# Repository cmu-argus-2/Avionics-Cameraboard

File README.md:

# camera-control-board
Board to control OpenMV Camera Clones.
The first draft of this board will be to create the interface between the MCU (the STM32H743IIT6) and the
similar QFP SDRAM chip, along with a USB and camera interface.

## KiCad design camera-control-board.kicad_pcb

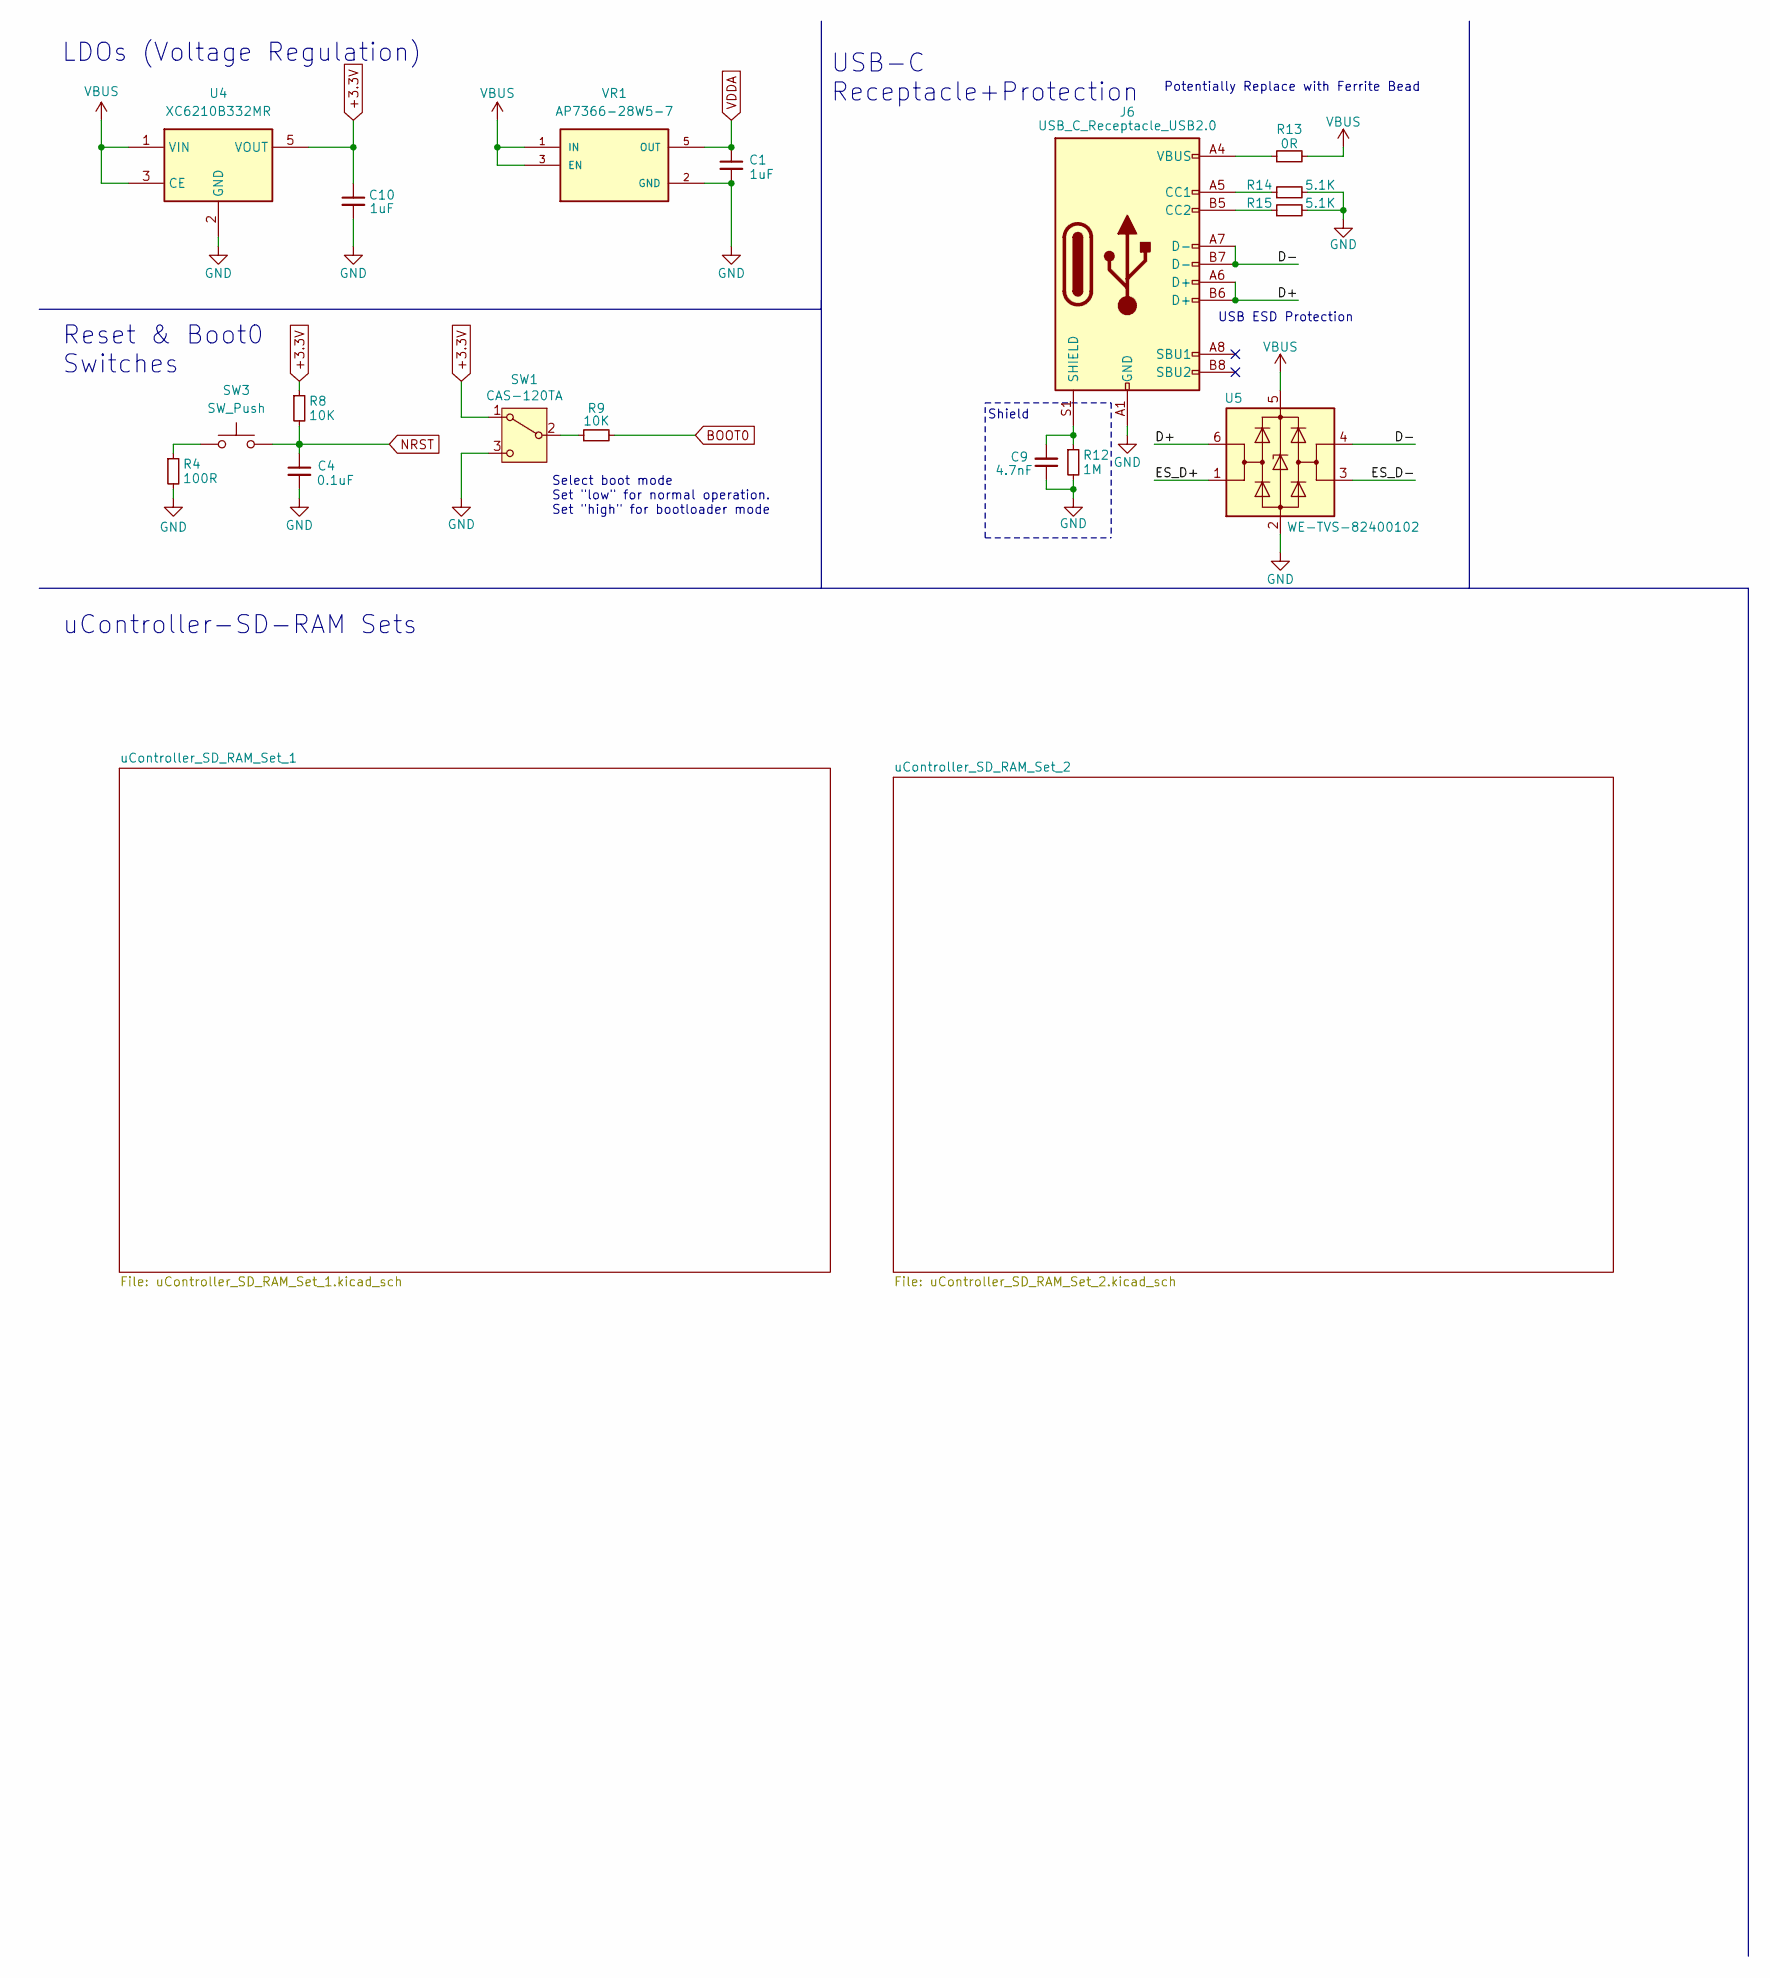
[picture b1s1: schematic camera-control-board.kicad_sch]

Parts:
C1, C10: 1uF; C_0603_1608Metric
C4: 0.1uF; C_0603_1608Metric
C9: 4.7nF; C_0603_1608Metric
J6: USB_C_Receptacle_USB2.0; USB_C_Receptacle_HRO_TYPE-C-31-M-12
R4: 100R; R_0603_1608Metric
R8, R9: 10K; R_0603_1608Metric
R12: 1M; R_0603_1608Metric
R13: 0R; R_0603_1608Metric
R14, R15: 5.1K; R_0603_1608Metric
SW1: CAS-120TA
SW3: SW_Push; BTN_KMR2
U4: XC6210B332MR; SOT-23-5
U5: WE-TVS-82400102; SOT-23-6
VR1: AP7366-28W5-7; SOT95P285X140-5N; PARTREV 1-2

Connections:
+3.3V: C10.1, R8.1, SW1.1 (A), U4.5 (VOUT); also elsewhere on the board
/D+: J6.A6 (D+), J6.B6 (D+), U5.6 (I/O1)
/D-: J6.A7 (D-), J6.B7 (D-), U5.4 (I/O2)
/ES_D+: U5.1 (I/O1)
/ES_D-: U5.3 (I/O2)
BOOT0: R9.2
GND: C1.2, C4.2, C9.1, C10.2, J6.A1 (GND), J6.A12 (GND), J6.B1 (GND), J6.B12 (GND), R4.2, R12.2, R14.2, R15.2, SW1.3 (C), U4.2 (GND), U5.2 (GND), VR1.2 (GND); also elsewhere on the board
NRST: C4.1, R8.2, SW3.2
unnamed: J6.A5 (CC1), R14.1
unnamed: J6.B5 (CC2), R15.1
unnamed: C9.2, J6.S1 (SHIELD), R12.1
unnamed: J6.A4 (VBUS), J6.A9 (VBUS), J6.B4 (VBUS), J6.B9 (VBUS), R13.1
unnamed: R4.1, SW3.1
unnamed: R9.1, SW1.2 (B)
VBUS: R13.2, U4.1 (VIN), U4.3 (CE), U5.5 (VBUS), VR1.1 (IN), VR1.3 (EN)
VDDA: C1.1, VR1.5 (OUT); also elsewhere on the board

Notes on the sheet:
LDOs (Voltage Regulation)
Shield
USB-C Receptacle+Protection
uController-SD-RAM Sets
Reset & Boot0 Switches
Potentially Replace with Ferrite Bead
USB ESD Protection
Select boot mode Set "low" for normal operation. Set "high" for bootloader mode

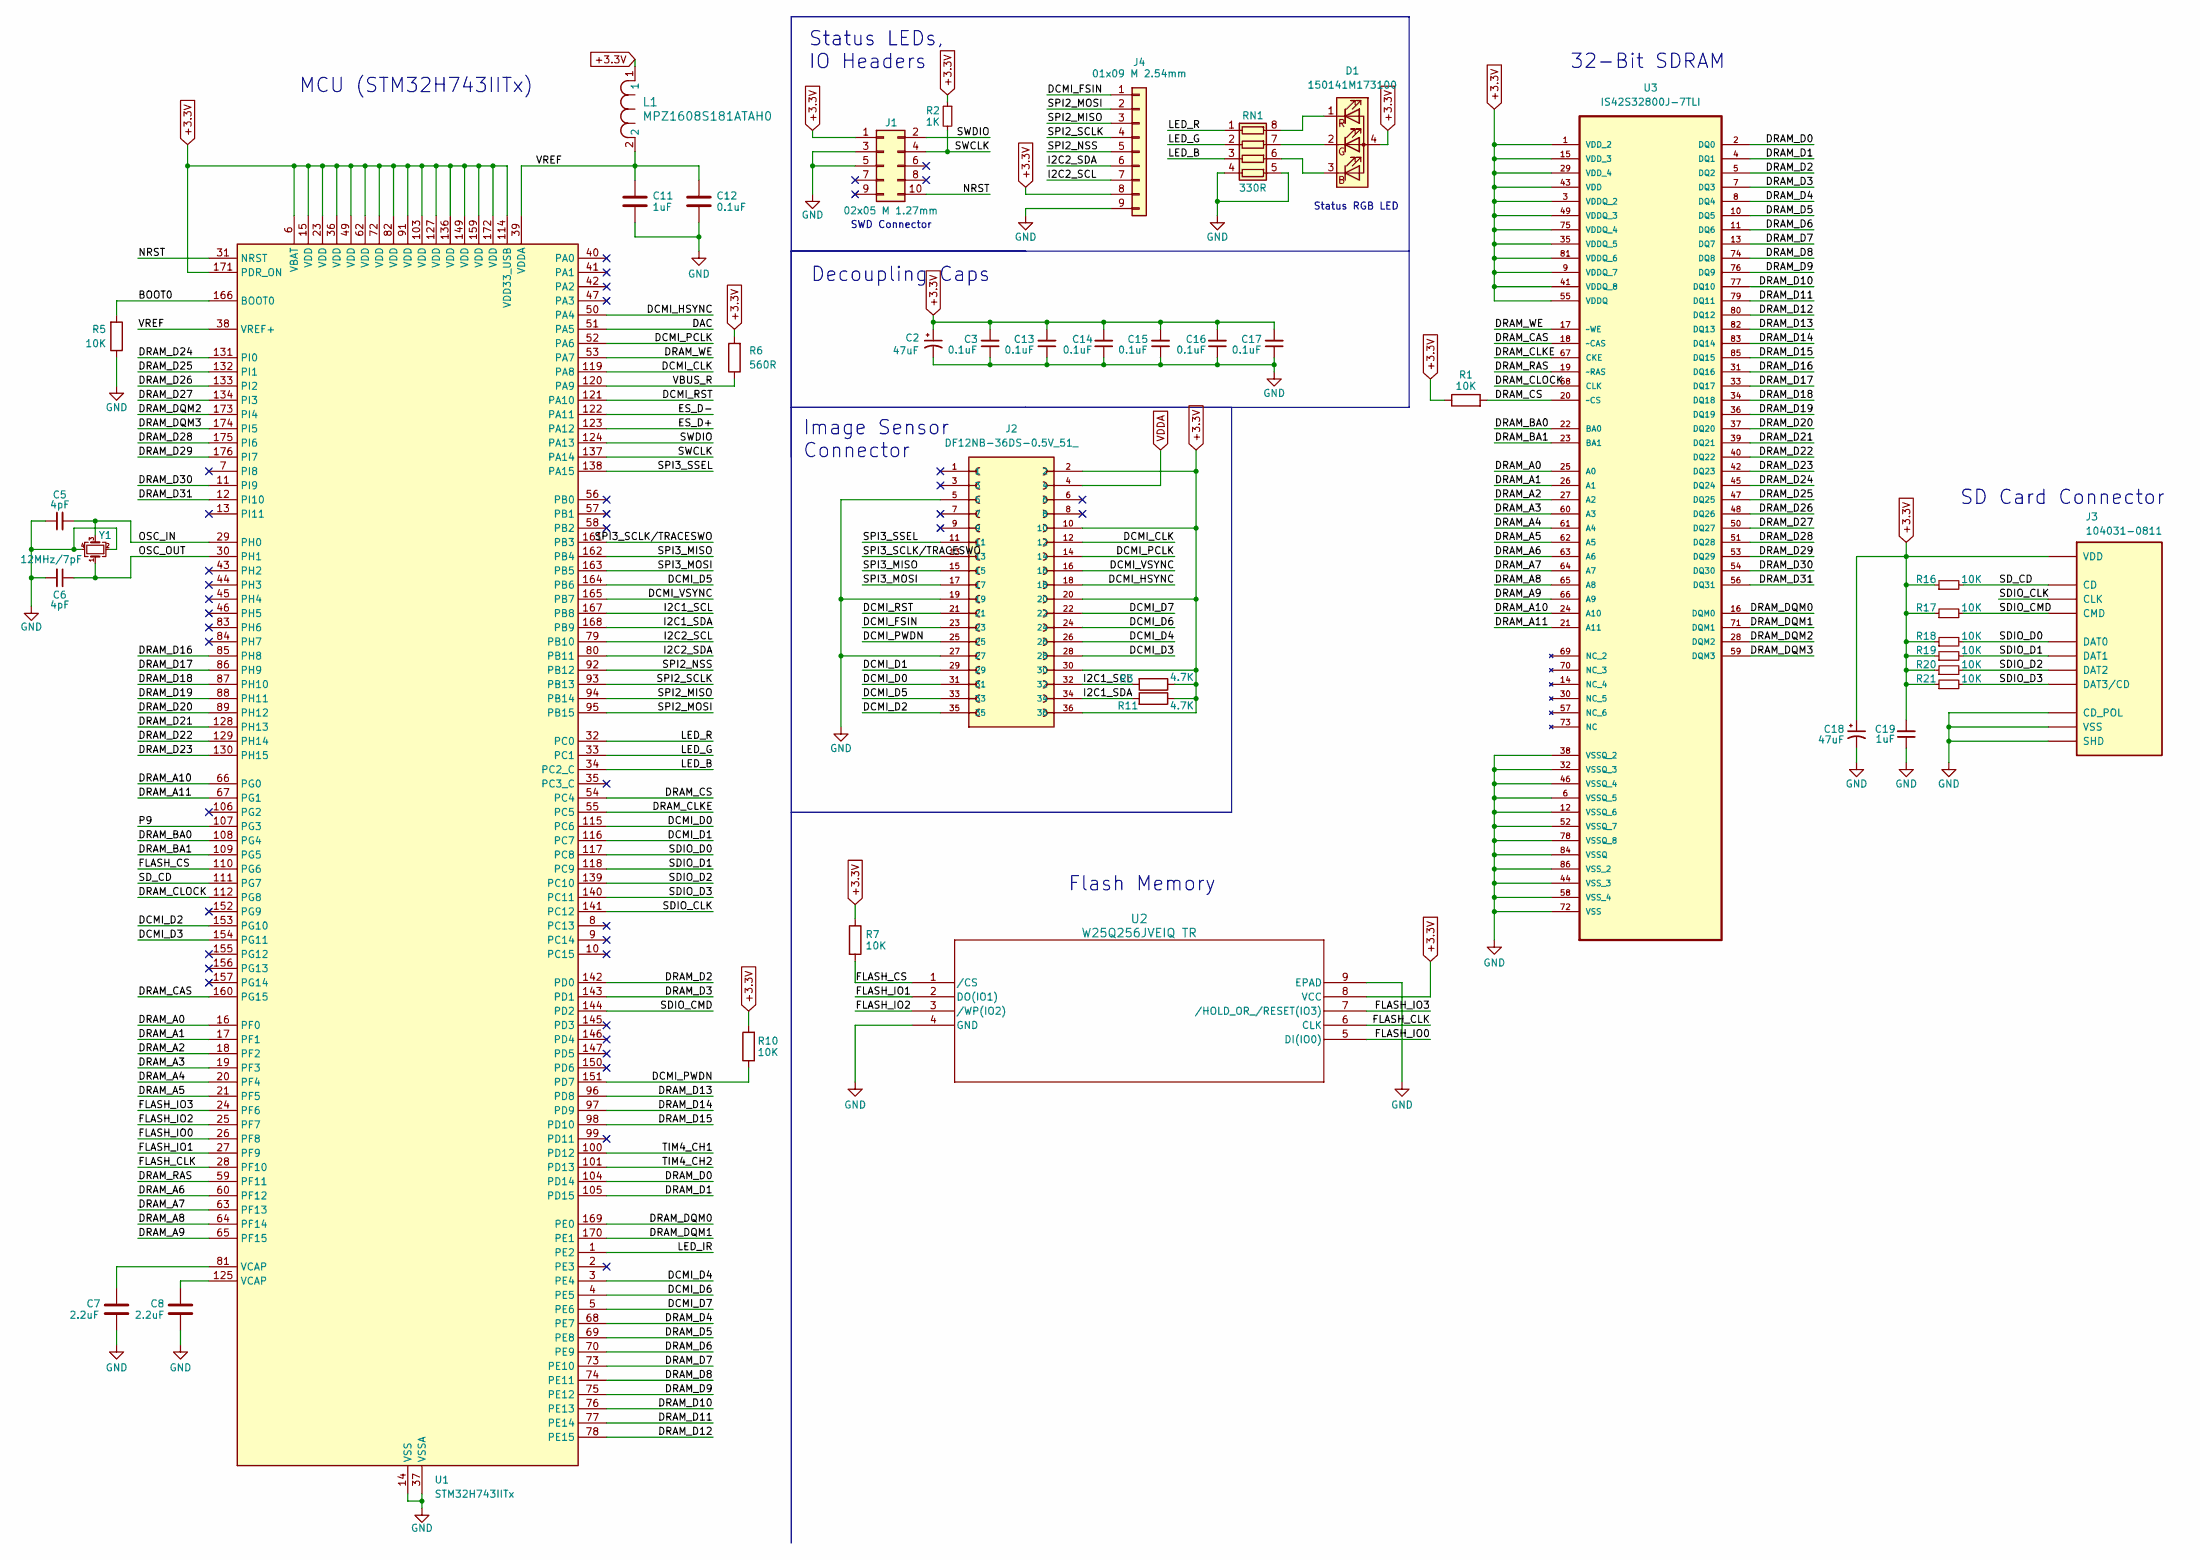
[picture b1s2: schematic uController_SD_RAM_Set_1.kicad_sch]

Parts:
C2, C18: 47uF; C_0805_2012Metric
C3, C12, C13, C14, C15, C16, C17: 0.1uF; C_0603_1608Metric
C5, C6: 4pF; C_0603_1608Metric
C7, C8: 2.2uF; C_0603_1608Metric
C11, C19: 1uF; C_0603_1608Metric
D1: 150141M173100; LED_RGB_Wuerth-PLCC4_3.2x2.8mm_150141M173100
J1: 02x05 M 1.27mm; PinHeader_2x05_P1.27mm_Vertical_SMD
J2: DF12NB-36DS-0.5V_51_; HRS_DF12NB-36DS-0.5V_51_
J3: 104031-0811; microSD_HC_Molex_104031-0811; PARTREV B2
J4: 01x09 M 2.54mm; PinHeader_1x09_P2.54mm_Vertical
L1: MPZ1608S181ATAH0; IND_1608_TDK
R1, R5, R7, R10, R16, R17, R18, R19, R20, R21: 10K; R_0603_1608Metric
R2: 1K; R_0603_1608Metric
R3, R11: 4.7K; R_0603_1608Metric
R6: 560R; R_0603_1608Metric
RN1: 330R; R_Array_Concave_4x0603
U1: STM32H743IITx; LQFP-176_24x24mm_P0.5mm
U2: W25Q256JVEIQ TR; WSON8_E_WIN-L
U3: IS42S32800J-7TLI; SOP50P1176X120-86N; MPN IS42S32800J-7TLI
Y1: 12MHz/7pF; Crystal_SMD_2520-4Pin_2.5x2.0mm

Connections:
+3.3V: C2.1, C3.2, C13.2, C14.2, C15.2, C16.2, C17.2, C18.1, C19.2, D1.4 (A), J1.1, J2.2, J2.10, J2.20, J2.30, J2.36, J3.4 (VDD), J4.8, L1.1, R1.1, R2.1, R3.1, R6.2, R7.1, R10.2, R11.1, R16.1, R17.1, R18.1, R19.1, R20.1, R21.1, U1.6 (VBAT), U1.15 (VDD), U1.23 (VDD), U1.36 (VDD), U1.49 (VDD), U1.62 (VDD), U1.72 (VDD), U1.82 (VDD), U1.91 (VDD), U1.103 (VDD), U1.114 (VDD33_USB), U1.127 (VDD), U1.136 (VDD), U1.149 (VDD), U1.159 (VDD), U1.171 (PDR_ON), U1.172 (VDD), U2.8 (VCC), U3.1 (VDD_2), U3.3 (VDDQ_2), U3.9 (VDDQ_7), U3.15 (VDD_3), U3.29 (VDD_4), U3.35 (VDDQ_5), U3.41 (VDDQ_8), U3.43 (VDD), U3.49 (VDDQ_3), U3.55 (VDDQ), U3.75 (VDDQ_4), U3.81 (VDDQ_6); also elsewhere on the board
/uController_SD_RAM_Set_1/BOOT0: R5.2, U1.166 (BOOT0)
/uController_SD_RAM_Set_1/DAC: U1.51 (PA5)
/uController_SD_RAM_Set_1/DCMI_CLK: J2.12, U1.119 (PA8)
/uController_SD_RAM_Set_1/DCMI_D0: J2.31, U1.115 (PC6)
/uController_SD_RAM_Set_1/DCMI_D1: J2.29, U1.116 (PC7)
/uController_SD_RAM_Set_1/DCMI_D2: J2.35, U1.153 (PG10)
/uController_SD_RAM_Set_1/DCMI_D3: J2.28, U1.154 (PG11)
/uController_SD_RAM_Set_1/DCMI_D4: J2.26, U1.3 (PE4)
/uController_SD_RAM_Set_1/DCMI_D5: J2.33, U1.164 (PB6)
/uController_SD_RAM_Set_1/DCMI_D6: J2.24, U1.4 (PE5)
/uController_SD_RAM_Set_1/DCMI_D7: J2.22, U1.5 (PE6)
/uController_SD_RAM_Set_1/DCMI_FSIN: J2.23, J4.1
/uController_SD_RAM_Set_1/DCMI_HSYNC: J2.18, U1.50 (PA4)
/uController_SD_RAM_Set_1/DCMI_PCLK: J2.14, U1.52 (PA6)
/uController_SD_RAM_Set_1/DCMI_PWDN: J2.25, R10.1, U1.151 (PD7)
/uController_SD_RAM_Set_1/DCMI_RST: J2.21, U1.121 (PA10)
/uController_SD_RAM_Set_1/DCMI_VSYNC: J2.16, U1.165 (PB7)
/uController_SD_RAM_Set_1/DRAM_A0: U1.16 (PF0), U3.25 (A0)
/uController_SD_RAM_Set_1/DRAM_A1: U1.17 (PF1), U3.26 (A1)
/uController_SD_RAM_Set_1/DRAM_A2: U1.18 (PF2), U3.27 (A2)
/uController_SD_RAM_Set_1/DRAM_A3: U1.19 (PF3), U3.60 (A3)
/uController_SD_RAM_Set_1/DRAM_A4: U1.20 (PF4), U3.61 (A4)
/uController_SD_RAM_Set_1/DRAM_A5: U1.21 (PF5), U3.62 (A5)
/uController_SD_RAM_Set_1/DRAM_A6: U1.60 (PF12), U3.63 (A6)
/uController_SD_RAM_Set_1/DRAM_A7: U1.63 (PF13), U3.64 (A7)
/uController_SD_RAM_Set_1/DRAM_A8: U1.64 (PF14), U3.65 (A8)
/uController_SD_RAM_Set_1/DRAM_A9: U1.65 (PF15), U3.66 (A9)
/uController_SD_RAM_Set_1/DRAM_A10: U1.66 (PG0), U3.24 (A10)
/uController_SD_RAM_Set_1/DRAM_A11: U1.67 (PG1), U3.21 (A11)
/uController_SD_RAM_Set_1/DRAM_BA0: U1.108 (PG4), U3.22 (BA0)
/uController_SD_RAM_Set_1/DRAM_BA1: U1.109 (PG5), U3.23 (BA1)
/uController_SD_RAM_Set_1/DRAM_CAS: U1.160 (PG15), U3.18 (~CAS)
/uController_SD_RAM_Set_1/DRAM_CLKE: U1.55 (PC5), U3.67 (CKE)
/uController_SD_RAM_Set_1/DRAM_CLOCK: U1.112 (PG8), U3.68 (CLK)
/uController_SD_RAM_Set_1/DRAM_CS: R1.2, U1.54 (PC4), U3.20 (~CS)
/uController_SD_RAM_Set_1/DRAM_D0: U1.104 (PD14), U3.2 (DQ0)
/uController_SD_RAM_Set_1/DRAM_D1: U1.105 (PD15), U3.4 (DQ1)
/uController_SD_RAM_Set_1/DRAM_D2: U1.142 (PD0), U3.5 (DQ2)
/uController_SD_RAM_Set_1/DRAM_D3: U1.143 (PD1), U3.7 (DQ3)
/uController_SD_RAM_Set_1/DRAM_D4: U1.68 (PE7), U3.8 (DQ4)
/uController_SD_RAM_Set_1/DRAM_D5: U1.69 (PE8), U3.10 (DQ5)
/uController_SD_RAM_Set_1/DRAM_D6: U1.70 (PE9), U3.11 (DQ6)
/uController_SD_RAM_Set_1/DRAM_D7: U1.73 (PE10), U3.13 (DQ7)
/uController_SD_RAM_Set_1/DRAM_D8: U1.74 (PE11), U3.74 (DQ8)
/uController_SD_RAM_Set_1/DRAM_D9: U1.75 (PE12), U3.76 (DQ9)
/uController_SD_RAM_Set_1/DRAM_D10: U1.76 (PE13), U3.77 (DQ10)
/uController_SD_RAM_Set_1/DRAM_D11: U1.77 (PE14), U3.79 (DQ11)
/uController_SD_RAM_Set_1/DRAM_D12: U1.78 (PE15), U3.80 (DQ12)
/uController_SD_RAM_Set_1/DRAM_D13: U1.96 (PD8), U3.82 (DQ13)
/uController_SD_RAM_Set_1/DRAM_D14: U1.97 (PD9), U3.83 (DQ14)
/uController_SD_RAM_Set_1/DRAM_D15: U1.98 (PD10), U3.85 (DQ15)
/uController_SD_RAM_Set_1/DRAM_D16: U1.85 (PH8), U3.31 (DQ16)
/uController_SD_RAM_Set_1/DRAM_D17: U1.86 (PH9), U3.33 (DQ17)
/uController_SD_RAM_Set_1/DRAM_D18: U1.87 (PH10), U3.34 (DQ18)
/uController_SD_RAM_Set_1/DRAM_D19: U1.88 (PH11), U3.36 (DQ19)
/uController_SD_RAM_Set_1/DRAM_D20: U1.89 (PH12), U3.37 (DQ20)
/uController_SD_RAM_Set_1/DRAM_D21: U1.128 (PH13), U3.39 (DQ21)
/uController_SD_RAM_Set_1/DRAM_D22: U1.129 (PH14), U3.40 (DQ22)
/uController_SD_RAM_Set_1/DRAM_D23: U1.130 (PH15), U3.42 (DQ23)
/uController_SD_RAM_Set_1/DRAM_D24: U1.131 (PI0), U3.45 (DQ24)
/uController_SD_RAM_Set_1/DRAM_D25: U1.132 (PI1), U3.47 (DQ25)
/uController_SD_RAM_Set_1/DRAM_D26: U1.133 (PI2), U3.48 (DQ26)
/uController_SD_RAM_Set_1/DRAM_D27: U1.134 (PI3), U3.50 (DQ27)
/uController_SD_RAM_Set_1/DRAM_D28: U1.175 (PI6), U3.51 (DQ28)
/uController_SD_RAM_Set_1/DRAM_D29: U1.176 (PI7), U3.53 (DQ29)
/uController_SD_RAM_Set_1/DRAM_D30: U1.11 (PI9), U3.54 (DQ30)
/uController_SD_RAM_Set_1/DRAM_D31: U1.12 (PI10), U3.56 (DQ31)
/uController_SD_RAM_Set_1/DRAM_DQM0: U1.169 (PE0), U3.16 (DQM0)
/uController_SD_RAM_Set_1/DRAM_DQM1: U1.170 (PE1), U3.71 (DQM1)
/uController_SD_RAM_Set_1/DRAM_DQM2: U1.173 (PI4), U3.28 (DQM2)
/uController_SD_RAM_Set_1/DRAM_DQM3: U1.174 (PI5), U3.59 (DQM3)
/uController_SD_RAM_Set_1/DRAM_RAS: U1.59 (PF11), U3.19 (~RAS)
/uController_SD_RAM_Set_1/DRAM_WE: U1.53 (PA7), U3.17 (~WE)
/uController_SD_RAM_Set_1/ES_D+: U1.123 (PA12)
/uController_SD_RAM_Set_1/ES_D-: U1.122 (PA11)
/uController_SD_RAM_Set_1/FLASH_CLK: U1.28 (PF10), U2.6 (CLK)
/uController_SD_RAM_Set_1/FLASH_CS: R7.2, U1.110 (PG6), U2.1 (/CS)
/uController_SD_RAM_Set_1/FLASH_IO0: U1.26 (PF8), U2.5 (DI(IO0))
/uController_SD_RAM_Set_1/FLASH_IO1: U1.27 (PF9), U2.2 (DO(IO1))
/uController_SD_RAM_Set_1/FLASH_IO2: U1.25 (PF7), U2.3 (/WP(IO2))
/uController_SD_RAM_Set_1/FLASH_IO3: U1.24 (PF6), U2.7 (/HOLD_OR_/RESET(IO3))
/uController_SD_RAM_Set_1/I2C1_SCL: J2.32, R3.2, U1.167 (PB8)
/uController_SD_RAM_Set_1/I2C1_SDA: J2.34, R11.2, U1.168 (PB9)
/uController_SD_RAM_Set_1/I2C2_SCL: J4.7, U1.79 (PB10)
/uController_SD_RAM_Set_1/I2C2_SDA: J4.6, U1.80 (PB11)
/uController_SD_RAM_Set_1/LED_B: RN1.3 (R3.1), U1.34 (PC2_C)
/uController_SD_RAM_Set_1/LED_G: RN1.2 (R2.1), U1.33 (PC1)
/uController_SD_RAM_Set_1/LED_IR: U1.1 (PE2)
/uController_SD_RAM_Set_1/LED_R: RN1.1 (R1.1), U1.32 (PC0)
/uController_SD_RAM_Set_1/NRST: J1.10, U1.31 (NRST)
/uController_SD_RAM_Set_1/OSC_IN: C5.2, U1.29 (PH0), Y1.3
/uController_SD_RAM_Set_1/OSC_OUT: C6.1, U1.30 (PH1), Y1.1
/uController_SD_RAM_Set_1/P9: U1.107 (PG3)
/uController_SD_RAM_Set_1/SDIO_CLK: J3.5 (CLK), U1.141 (PC12)
/uController_SD_RAM_Set_1/SDIO_CMD: J3.3 (CMD), R17.2, U1.144 (PD2)
/uController_SD_RAM_Set_1/SDIO_D0: J3.7 (DAT0), R18.2, U1.117 (PC8)
/uController_SD_RAM_Set_1/SDIO_D1: J3.8 (DAT1), R19.2, U1.118 (PC9)
/uController_SD_RAM_Set_1/SDIO_D2: J3.1 (DAT2), R20.2, U1.139 (PC10)
/uController_SD_RAM_Set_1/SDIO_D3: J3.2 (DAT3/CD), R21.2, U1.140 (PC11)
/uController_SD_RAM_Set_1/SD_CD: J3.10 (CD), R16.2, U1.111 (PG7)
/uController_SD_RAM_Set_1/SPI2_MISO: J4.3, U1.94 (PB14)
/uController_SD_RAM_Set_1/SPI2_MOSI: J4.2, U1.95 (PB15)
/uController_SD_RAM_Set_1/SPI2_NSS: J4.5, U1.92 (PB12)
/uController_SD_RAM_Set_1/SPI2_SCLK: J4.4, U1.93 (PB13)
/uController_SD_RAM_Set_1/SPI3_MISO: J2.15, U1.162 (PB4)
/uController_SD_RAM_Set_1/SPI3_MOSI: J2.17, U1.163 (PB5)
/uController_SD_RAM_Set_1/SPI3_SCLK/TRACESWO: J2.13, U1.161 (PB3)
/uController_SD_RAM_Set_1/SPI3_SSEL: J2.11, U1.138 (PA15)
/uController_SD_RAM_Set_1/SWCLK: J1.4, R2.2, U1.137 (PA14)
/uController_SD_RAM_Set_1/SWDIO: J1.2, U1.124 (PA13)
/uController_SD_RAM_Set_1/TIM4_CH1: U1.100 (PD12)
/uController_SD_RAM_Set_1/TIM4_CH2: U1.101 (PD13)
/uController_SD_RAM_Set_1/VBUS_R: R6.1, U1.120 (PA9)
/uController_SD_RAM_Set_1/VREF: C11.1, C12.1, L1.2, U1.38 (VREF+), U1.39 (VDDA)
GND: C2.2, C3.1, C5.1, C6.2, C7.2, C8.2, C11.2, C12.2, C13.1, C14.1, C15.1, C16.1, C17.1, C18.2, C19.1, J1.3, J1.5, J2.5, J2.19, J2.27, J3.6 (VSS), J3.9 (CD_POL), J3.11 (SHD), J4.9, R5.1, RN1.4 (R4.1), RN1.5 (R4.2), U1.14 (VSS), U1.22 (VSS), U1.37 (VSSA), U1.48 (VSS), U1.61 (VSS), U1.71 (VSS), U1.90 (VSS), U1.102 (VSS), U1.113 (VSS), U1.126 (VSS), U1.135 (VSS), U1.148 (VSS), U1.158 (VSS), U2.4 (GND), U2.9 (EPAD), U3.6 (VSSQ_5), U3.12 (VSSQ_6), U3.32 (VSSQ_3), U3.38 (VSSQ_2), U3.44 (VSS_3), U3.46 (VSSQ_4), U3.52 (VSSQ_7), U3.58 (VSS_4), U3.72 (VSS), U3.78 (VSSQ_8), U3.84 (VSSQ), U3.86 (VSS_2), Y1.2, Y1.4; also elsewhere on the board
unnamed: C7.1, U1.81 (VCAP)
unnamed: C8.1, U1.125 (VCAP)
unnamed: D1.3 (BK), RN1.6 (R3.2)
unnamed: D1.2 (GK), RN1.7 (R2.2)
unnamed: D1.1 (RK), RN1.8 (R1.2)
VDDA: J2.4; also elsewhere on the board

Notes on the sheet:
Decoupling Caps
Image Sensor Connector
Flash Memory
Status LEDs, IO Headers
SD Card Connector
SWD Connector
32-Bit SDRAM
Status RGB LED
MCU (STM32H743IITx)

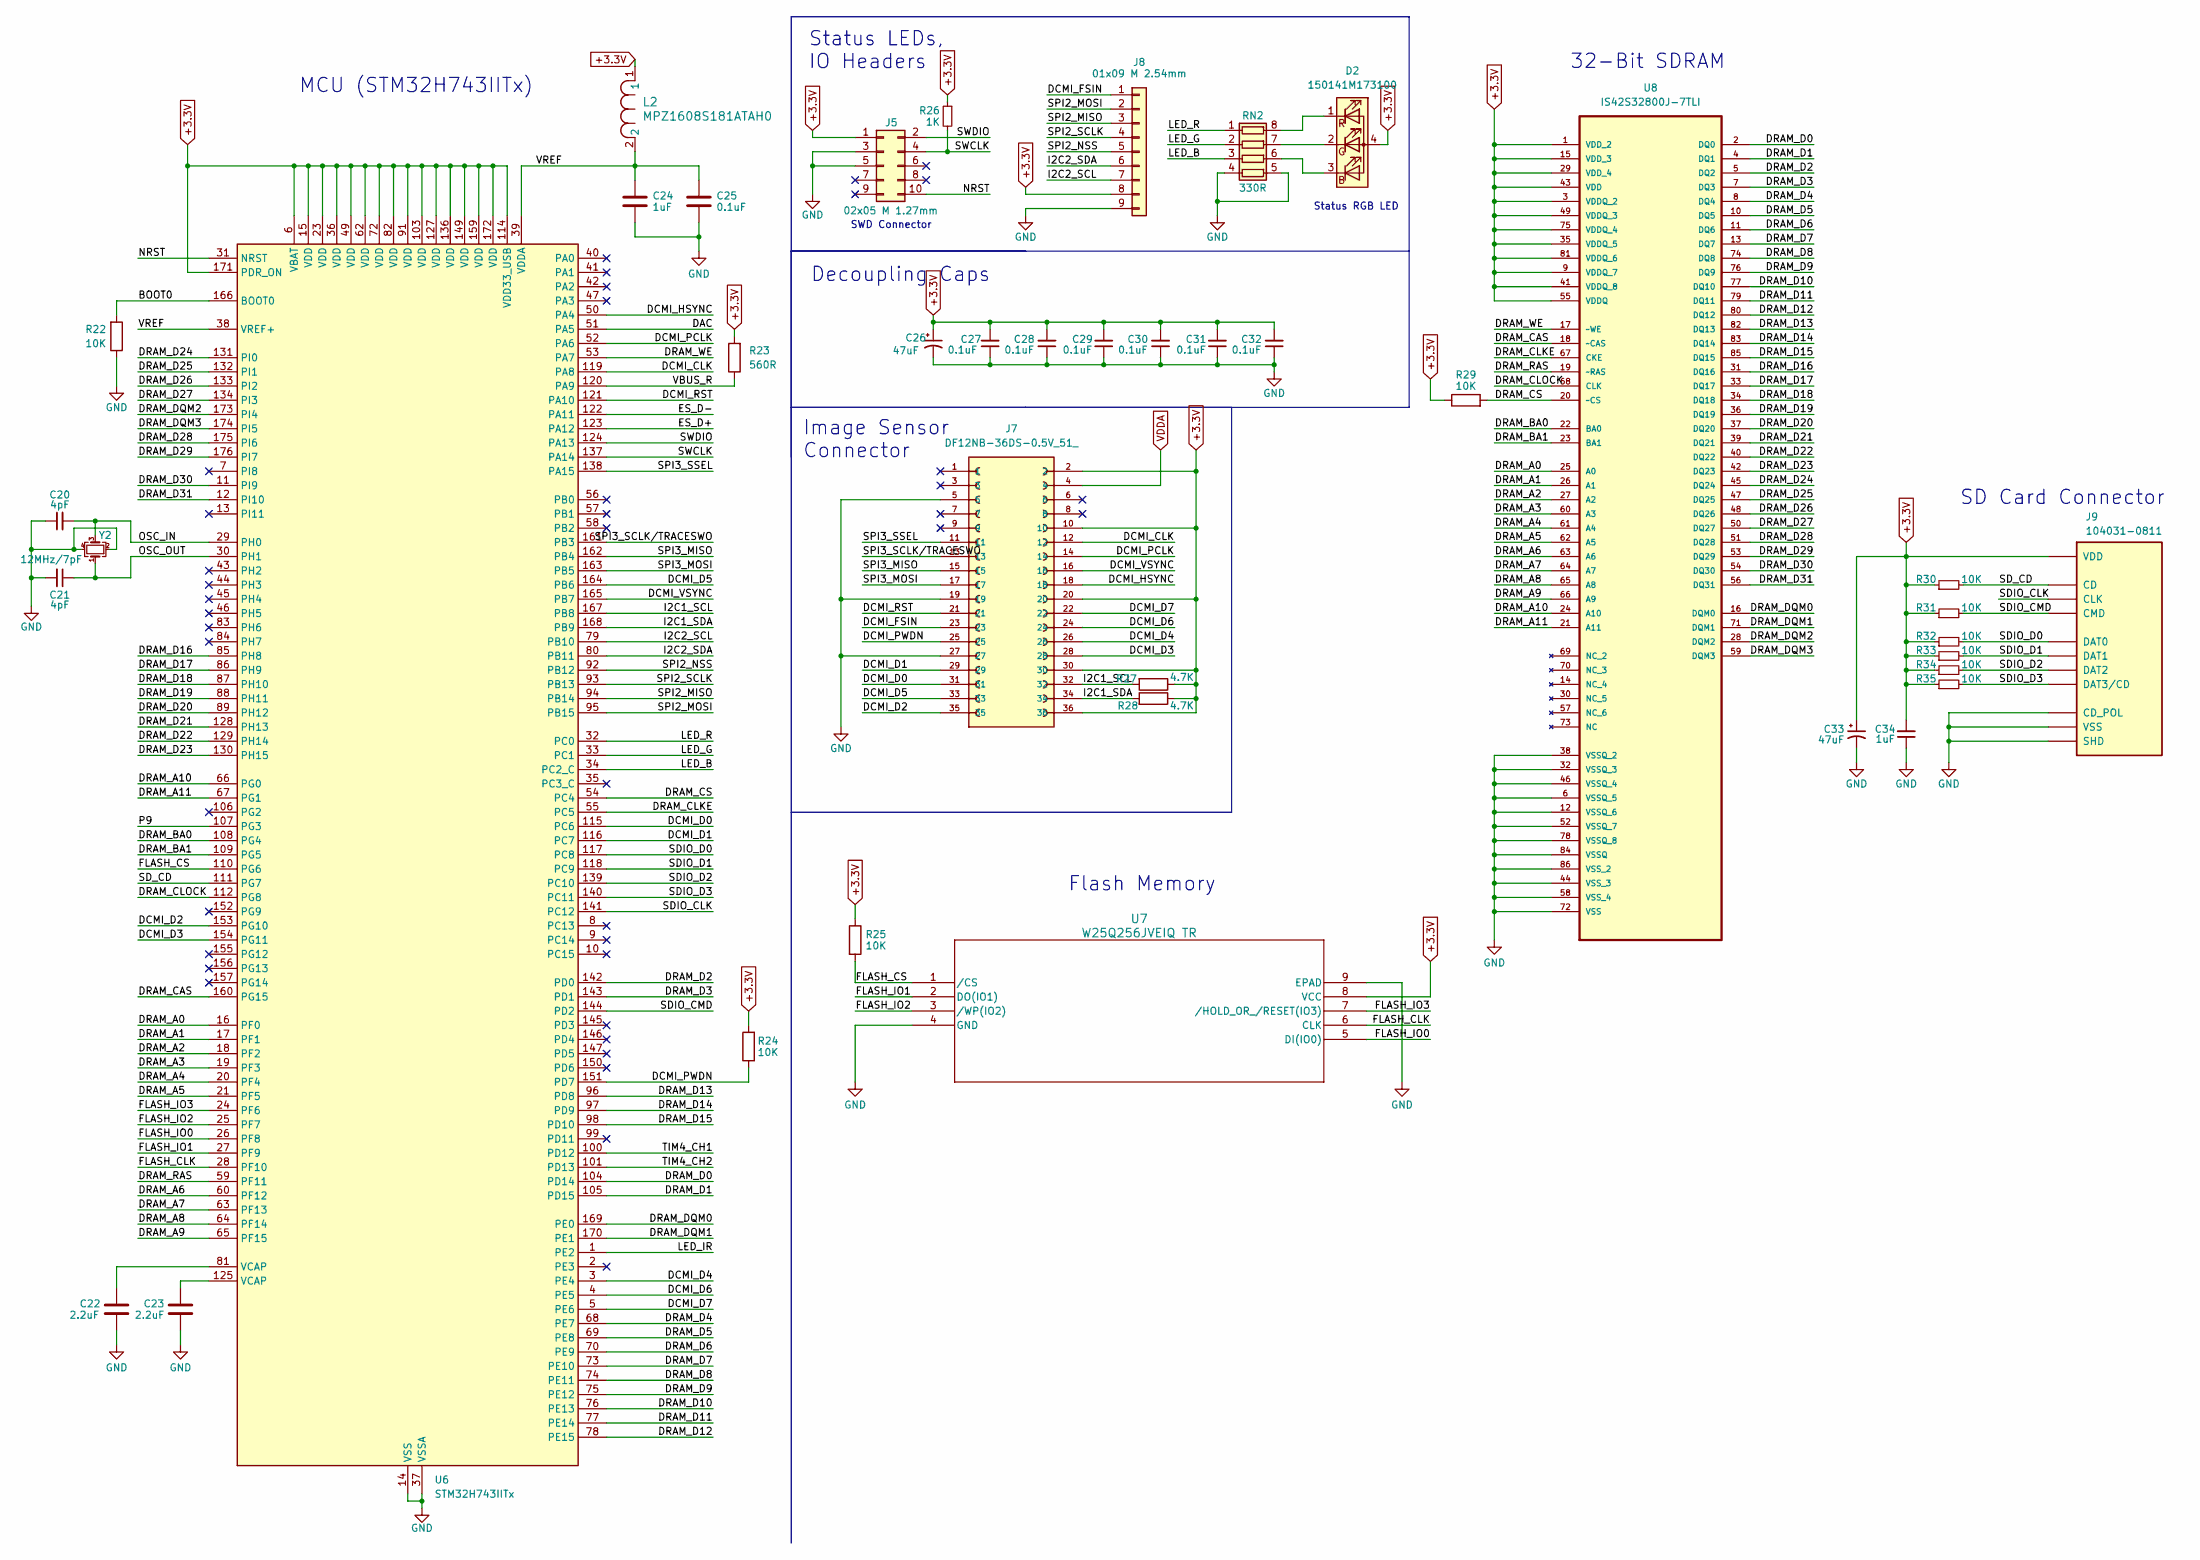
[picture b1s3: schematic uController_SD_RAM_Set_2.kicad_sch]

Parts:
C20, C21: 4pF; C_0603_1608Metric
C22, C23: 2.2uF; C_0603_1608Metric
C24, C34: 1uF; C_0603_1608Metric
C25, C27, C28, C29, C30, C31, C32: 0.1uF; C_0603_1608Metric
C26, C33: 47uF; C_0805_2012Metric
D2: 150141M173100; LED_RGB_Wuerth-PLCC4_3.2x2.8mm_150141M173100
J5: 02x05 M 1.27mm; PinHeader_2x05_P1.27mm_Vertical_SMD
J7: DF12NB-36DS-0.5V_51_; HRS_DF12NB-36DS-0.5V_51_
J8: 01x09 M 2.54mm; PinHeader_1x09_P2.54mm_Vertical
J9: 104031-0811; microSD_HC_Molex_104031-0811; PARTREV B2
L2: MPZ1608S181ATAH0; IND_1608_TDK
R22, R24, R25, R29, R30, R31, R32, R33, R34, R35: 10K; R_0603_1608Metric
R23: 560R; R_0603_1608Metric
R26: 1K; R_0603_1608Metric
R27, R28: 4.7K; R_0603_1608Metric
RN2: 330R; R_Array_Concave_4x0603
U6: STM32H743IITx; LQFP-176_24x24mm_P0.5mm
U7: W25Q256JVEIQ TR; WSON8_E_WIN-L
U8: IS42S32800J-7TLI; SOP50P1176X120-86N; MPN IS42S32800J-7TLI
Y2: 12MHz/7pF; Crystal_SMD_2520-4Pin_2.5x2.0mm

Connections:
+3.3V: C26.1, C27.2, C28.2, C29.2, C30.2, C31.2, C32.2, C33.1, C34.2, D2.4 (A), J5.1, J7.2, J7.10, J7.20, J7.30, J7.36, J8.8, J9.4 (VDD), L2.1, R23.2, R24.2, R25.1, R26.1, R27.1, R28.1, R29.1, R30.1, R31.1, R32.1, R33.1, R34.1, R35.1, U6.6 (VBAT), U6.15 (VDD), U6.23 (VDD), U6.36 (VDD), U6.49 (VDD), U6.62 (VDD), U6.72 (VDD), U6.82 (VDD), U6.91 (VDD), U6.103 (VDD), U6.114 (VDD33_USB), U6.127 (VDD), U6.136 (VDD), U6.149 (VDD), U6.159 (VDD), U6.171 (PDR_ON), U6.172 (VDD), U7.8 (VCC), U8.1 (VDD_2), U8.3 (VDDQ_2), U8.9 (VDDQ_7), U8.15 (VDD_3), U8.29 (VDD_4), U8.35 (VDDQ_5), U8.41 (VDDQ_8), U8.43 (VDD), U8.49 (VDDQ_3), U8.55 (VDDQ), U8.75 (VDDQ_4), U8.81 (VDDQ_6); also elsewhere on the board
/uController_SD_RAM_Set_2/BOOT0: R22.2, U6.166 (BOOT0)
/uController_SD_RAM_Set_2/DAC: U6.51 (PA5)
/uController_SD_RAM_Set_2/DCMI_CLK: J7.12, U6.119 (PA8)
/uController_SD_RAM_Set_2/DCMI_D0: J7.31, U6.115 (PC6)
/uController_SD_RAM_Set_2/DCMI_D1: J7.29, U6.116 (PC7)
/uController_SD_RAM_Set_2/DCMI_D2: J7.35, U6.153 (PG10)
/uController_SD_RAM_Set_2/DCMI_D3: J7.28, U6.154 (PG11)
/uController_SD_RAM_Set_2/DCMI_D4: J7.26, U6.3 (PE4)
/uController_SD_RAM_Set_2/DCMI_D5: J7.33, U6.164 (PB6)
/uController_SD_RAM_Set_2/DCMI_D6: J7.24, U6.4 (PE5)
/uController_SD_RAM_Set_2/DCMI_D7: J7.22, U6.5 (PE6)
/uController_SD_RAM_Set_2/DCMI_FSIN: J7.23, J8.1
/uController_SD_RAM_Set_2/DCMI_HSYNC: J7.18, U6.50 (PA4)
/uController_SD_RAM_Set_2/DCMI_PCLK: J7.14, U6.52 (PA6)
/uController_SD_RAM_Set_2/DCMI_PWDN: J7.25, R24.1, U6.151 (PD7)
/uController_SD_RAM_Set_2/DCMI_RST: J7.21, U6.121 (PA10)
/uController_SD_RAM_Set_2/DCMI_VSYNC: J7.16, U6.165 (PB7)
/uController_SD_RAM_Set_2/DRAM_A0: U6.16 (PF0), U8.25 (A0)
/uController_SD_RAM_Set_2/DRAM_A1: U6.17 (PF1), U8.26 (A1)
/uController_SD_RAM_Set_2/DRAM_A2: U6.18 (PF2), U8.27 (A2)
/uController_SD_RAM_Set_2/DRAM_A3: U6.19 (PF3), U8.60 (A3)
/uController_SD_RAM_Set_2/DRAM_A4: U6.20 (PF4), U8.61 (A4)
/uController_SD_RAM_Set_2/DRAM_A5: U6.21 (PF5), U8.62 (A5)
/uController_SD_RAM_Set_2/DRAM_A6: U6.60 (PF12), U8.63 (A6)
/uController_SD_RAM_Set_2/DRAM_A7: U6.63 (PF13), U8.64 (A7)
/uController_SD_RAM_Set_2/DRAM_A8: U6.64 (PF14), U8.65 (A8)
/uController_SD_RAM_Set_2/DRAM_A9: U6.65 (PF15), U8.66 (A9)
/uController_SD_RAM_Set_2/DRAM_A10: U6.66 (PG0), U8.24 (A10)
/uController_SD_RAM_Set_2/DRAM_A11: U6.67 (PG1), U8.21 (A11)
/uController_SD_RAM_Set_2/DRAM_BA0: U6.108 (PG4), U8.22 (BA0)
/uController_SD_RAM_Set_2/DRAM_BA1: U6.109 (PG5), U8.23 (BA1)
/uController_SD_RAM_Set_2/DRAM_CAS: U6.160 (PG15), U8.18 (~CAS)
/uController_SD_RAM_Set_2/DRAM_CLKE: U6.55 (PC5), U8.67 (CKE)
/uController_SD_RAM_Set_2/DRAM_CLOCK: U6.112 (PG8), U8.68 (CLK)
/uController_SD_RAM_Set_2/DRAM_CS: R29.2, U6.54 (PC4), U8.20 (~CS)
/uController_SD_RAM_Set_2/DRAM_D0: U6.104 (PD14), U8.2 (DQ0)
/uController_SD_RAM_Set_2/DRAM_D1: U6.105 (PD15), U8.4 (DQ1)
/uController_SD_RAM_Set_2/DRAM_D2: U6.142 (PD0), U8.5 (DQ2)
/uController_SD_RAM_Set_2/DRAM_D3: U6.143 (PD1), U8.7 (DQ3)
/uController_SD_RAM_Set_2/DRAM_D4: U6.68 (PE7), U8.8 (DQ4)
/uController_SD_RAM_Set_2/DRAM_D5: U6.69 (PE8), U8.10 (DQ5)
/uController_SD_RAM_Set_2/DRAM_D6: U6.70 (PE9), U8.11 (DQ6)
/uController_SD_RAM_Set_2/DRAM_D7: U6.73 (PE10), U8.13 (DQ7)
/uController_SD_RAM_Set_2/DRAM_D8: U6.74 (PE11), U8.74 (DQ8)
/uController_SD_RAM_Set_2/DRAM_D9: U6.75 (PE12), U8.76 (DQ9)
/uController_SD_RAM_Set_2/DRAM_D10: U6.76 (PE13), U8.77 (DQ10)
/uController_SD_RAM_Set_2/DRAM_D11: U6.77 (PE14), U8.79 (DQ11)
/uController_SD_RAM_Set_2/DRAM_D12: U6.78 (PE15), U8.80 (DQ12)
/uController_SD_RAM_Set_2/DRAM_D13: U6.96 (PD8), U8.82 (DQ13)
/uController_SD_RAM_Set_2/DRAM_D14: U6.97 (PD9), U8.83 (DQ14)
/uController_SD_RAM_Set_2/DRAM_D15: U6.98 (PD10), U8.85 (DQ15)
/uController_SD_RAM_Set_2/DRAM_D16: U6.85 (PH8), U8.31 (DQ16)
/uController_SD_RAM_Set_2/DRAM_D17: U6.86 (PH9), U8.33 (DQ17)
/uController_SD_RAM_Set_2/DRAM_D18: U6.87 (PH10), U8.34 (DQ18)
/uController_SD_RAM_Set_2/DRAM_D19: U6.88 (PH11), U8.36 (DQ19)
/uController_SD_RAM_Set_2/DRAM_D20: U6.89 (PH12), U8.37 (DQ20)
/uController_SD_RAM_Set_2/DRAM_D21: U6.128 (PH13), U8.39 (DQ21)
/uController_SD_RAM_Set_2/DRAM_D22: U6.129 (PH14), U8.40 (DQ22)
/uController_SD_RAM_Set_2/DRAM_D23: U6.130 (PH15), U8.42 (DQ23)
/uController_SD_RAM_Set_2/DRAM_D24: U6.131 (PI0), U8.45 (DQ24)
/uController_SD_RAM_Set_2/DRAM_D25: U6.132 (PI1), U8.47 (DQ25)
/uController_SD_RAM_Set_2/DRAM_D26: U6.133 (PI2), U8.48 (DQ26)
/uController_SD_RAM_Set_2/DRAM_D27: U6.134 (PI3), U8.50 (DQ27)
/uController_SD_RAM_Set_2/DRAM_D28: U6.175 (PI6), U8.51 (DQ28)
/uController_SD_RAM_Set_2/DRAM_D29: U6.176 (PI7), U8.53 (DQ29)
/uController_SD_RAM_Set_2/DRAM_D30: U6.11 (PI9), U8.54 (DQ30)
/uController_SD_RAM_Set_2/DRAM_D31: U6.12 (PI10), U8.56 (DQ31)
/uController_SD_RAM_Set_2/DRAM_DQM0: U6.169 (PE0), U8.16 (DQM0)
/uController_SD_RAM_Set_2/DRAM_DQM1: U6.170 (PE1), U8.71 (DQM1)
/uController_SD_RAM_Set_2/DRAM_DQM2: U6.173 (PI4), U8.28 (DQM2)
/uController_SD_RAM_Set_2/DRAM_DQM3: U6.174 (PI5), U8.59 (DQM3)
/uController_SD_RAM_Set_2/DRAM_RAS: U6.59 (PF11), U8.19 (~RAS)
/uController_SD_RAM_Set_2/DRAM_WE: U6.53 (PA7), U8.17 (~WE)
/uController_SD_RAM_Set_2/ES_D+: U6.123 (PA12)
/uController_SD_RAM_Set_2/ES_D-: U6.122 (PA11)
/uController_SD_RAM_Set_2/FLASH_CLK: U6.28 (PF10), U7.6 (CLK)
/uController_SD_RAM_Set_2/FLASH_CS: R25.2, U6.110 (PG6), U7.1 (/CS)
/uController_SD_RAM_Set_2/FLASH_IO0: U6.26 (PF8), U7.5 (DI(IO0))
/uController_SD_RAM_Set_2/FLASH_IO1: U6.27 (PF9), U7.2 (DO(IO1))
/uController_SD_RAM_Set_2/FLASH_IO2: U6.25 (PF7), U7.3 (/WP(IO2))
/uController_SD_RAM_Set_2/FLASH_IO3: U6.24 (PF6), U7.7 (/HOLD_OR_/RESET(IO3))
/uController_SD_RAM_Set_2/I2C1_SCL: J7.32, R27.2, U6.167 (PB8)
/uController_SD_RAM_Set_2/I2C1_SDA: J7.34, R28.2, U6.168 (PB9)
/uController_SD_RAM_Set_2/I2C2_SCL: J8.7, U6.79 (PB10)
/uController_SD_RAM_Set_2/I2C2_SDA: J8.6, U6.80 (PB11)
/uController_SD_RAM_Set_2/LED_B: RN2.3 (R3.1), U6.34 (PC2_C)
/uController_SD_RAM_Set_2/LED_G: RN2.2 (R2.1), U6.33 (PC1)
/uController_SD_RAM_Set_2/LED_IR: U6.1 (PE2)
/uController_SD_RAM_Set_2/LED_R: RN2.1 (R1.1), U6.32 (PC0)
/uController_SD_RAM_Set_2/NRST: J5.10, U6.31 (NRST)
/uController_SD_RAM_Set_2/OSC_IN: C20.2, U6.29 (PH0), Y2.3
/uController_SD_RAM_Set_2/OSC_OUT: C21.1, U6.30 (PH1), Y2.1
/uController_SD_RAM_Set_2/P9: U6.107 (PG3)
/uController_SD_RAM_Set_2/SDIO_CLK: J9.5 (CLK), U6.141 (PC12)
/uController_SD_RAM_Set_2/SDIO_CMD: J9.3 (CMD), R31.2, U6.144 (PD2)
/uController_SD_RAM_Set_2/SDIO_D0: J9.7 (DAT0), R32.2, U6.117 (PC8)
/uController_SD_RAM_Set_2/SDIO_D1: J9.8 (DAT1), R33.2, U6.118 (PC9)
/uController_SD_RAM_Set_2/SDIO_D2: J9.1 (DAT2), R34.2, U6.139 (PC10)
/uController_SD_RAM_Set_2/SDIO_D3: J9.2 (DAT3/CD), R35.2, U6.140 (PC11)
/uController_SD_RAM_Set_2/SD_CD: J9.10 (CD), R30.2, U6.111 (PG7)
/uController_SD_RAM_Set_2/SPI2_MISO: J8.3, U6.94 (PB14)
/uController_SD_RAM_Set_2/SPI2_MOSI: J8.2, U6.95 (PB15)
/uController_SD_RAM_Set_2/SPI2_NSS: J8.5, U6.92 (PB12)
/uController_SD_RAM_Set_2/SPI2_SCLK: J8.4, U6.93 (PB13)
/uController_SD_RAM_Set_2/SPI3_MISO: J7.15, U6.162 (PB4)
/uController_SD_RAM_Set_2/SPI3_MOSI: J7.17, U6.163 (PB5)
/uController_SD_RAM_Set_2/SPI3_SCLK/TRACESWO: J7.13, U6.161 (PB3)
/uController_SD_RAM_Set_2/SPI3_SSEL: J7.11, U6.138 (PA15)
/uController_SD_RAM_Set_2/SWCLK: J5.4, R26.2, U6.137 (PA14)
/uController_SD_RAM_Set_2/SWDIO: J5.2, U6.124 (PA13)
/uController_SD_RAM_Set_2/TIM4_CH1: U6.100 (PD12)
/uController_SD_RAM_Set_2/TIM4_CH2: U6.101 (PD13)
/uController_SD_RAM_Set_2/VBUS_R: R23.1, U6.120 (PA9)
/uController_SD_RAM_Set_2/VREF: C24.1, C25.1, L2.2, U6.38 (VREF+), U6.39 (VDDA)
GND: C20.1, C21.2, C22.2, C23.2, C24.2, C25.2, C26.2, C27.1, C28.1, C29.1, C30.1, C31.1, C32.1, C33.2, C34.1, J5.3, J5.5, J7.5, J7.19, J7.27, J8.9, J9.6 (VSS), J9.9 (CD_POL), J9.11 (SHD), R22.1, RN2.4 (R4.1), RN2.5 (R4.2), U6.14 (VSS), U6.22 (VSS), U6.37 (VSSA), U6.48 (VSS), U6.61 (VSS), U6.71 (VSS), U6.90 (VSS), U6.102 (VSS), U6.113 (VSS), U6.126 (VSS), U6.135 (VSS), U6.148 (VSS), U6.158 (VSS), U7.4 (GND), U7.9 (EPAD), U8.6 (VSSQ_5), U8.12 (VSSQ_6), U8.32 (VSSQ_3), U8.38 (VSSQ_2), U8.44 (VSS_3), U8.46 (VSSQ_4), U8.52 (VSSQ_7), U8.58 (VSS_4), U8.72 (VSS), U8.78 (VSSQ_8), U8.84 (VSSQ), U8.86 (VSS_2), Y2.2, Y2.4; also elsewhere on the board
unnamed: C22.1, U6.81 (VCAP)
unnamed: C23.1, U6.125 (VCAP)
unnamed: D2.3 (BK), RN2.6 (R3.2)
unnamed: D2.2 (GK), RN2.7 (R2.2)
unnamed: D2.1 (RK), RN2.8 (R1.2)
VDDA: J7.4; also elsewhere on the board

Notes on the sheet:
SWD Connector
32-Bit SDRAM
Flash Memory
Status RGB LED
MCU (STM32H743IITx)
Decoupling Caps
Status LEDs, IO Headers
Image Sensor Connector
SD Card Connector
